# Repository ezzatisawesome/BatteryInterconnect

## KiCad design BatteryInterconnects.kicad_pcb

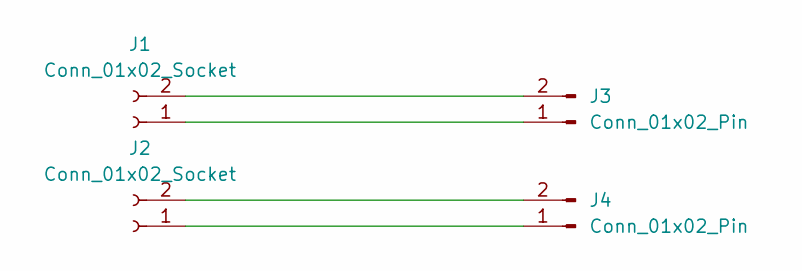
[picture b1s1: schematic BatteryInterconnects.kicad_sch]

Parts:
J1, J2: Conn_01x02_Socket; AMASS_XT30U-F_1x02_P5.0mm_Vertical; Mfr P/N XT30PW-F
J3, J4: Conn_01x02_Pin; AMASS_XT30U-M_1x02_P5.0mm_Vertical; Mfr P/N XT30PW-M

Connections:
unnamed: J1.1, J3.1
unnamed: J1.2, J3.2
unnamed: J2.1, J4.1
unnamed: J2.2, J4.2

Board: 2 copper layers, 4 parts (0 on the bottom side), 4 nets, no tracks yet.

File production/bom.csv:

Designator,Footprint,Quantity,Value,LCSC Part #
"J1, J2",AMASS_XT30U-F_1x02_P5.0mm_Vertical,2,Conn_01x02_Socket,
"J3, J4",AMASS_XT30U-M_1x02_P5.0mm_Vertical,2,Conn_01x02_Pin,

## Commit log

2026-01-20 Stuff
2026-01-21 Tweaks and Production files
